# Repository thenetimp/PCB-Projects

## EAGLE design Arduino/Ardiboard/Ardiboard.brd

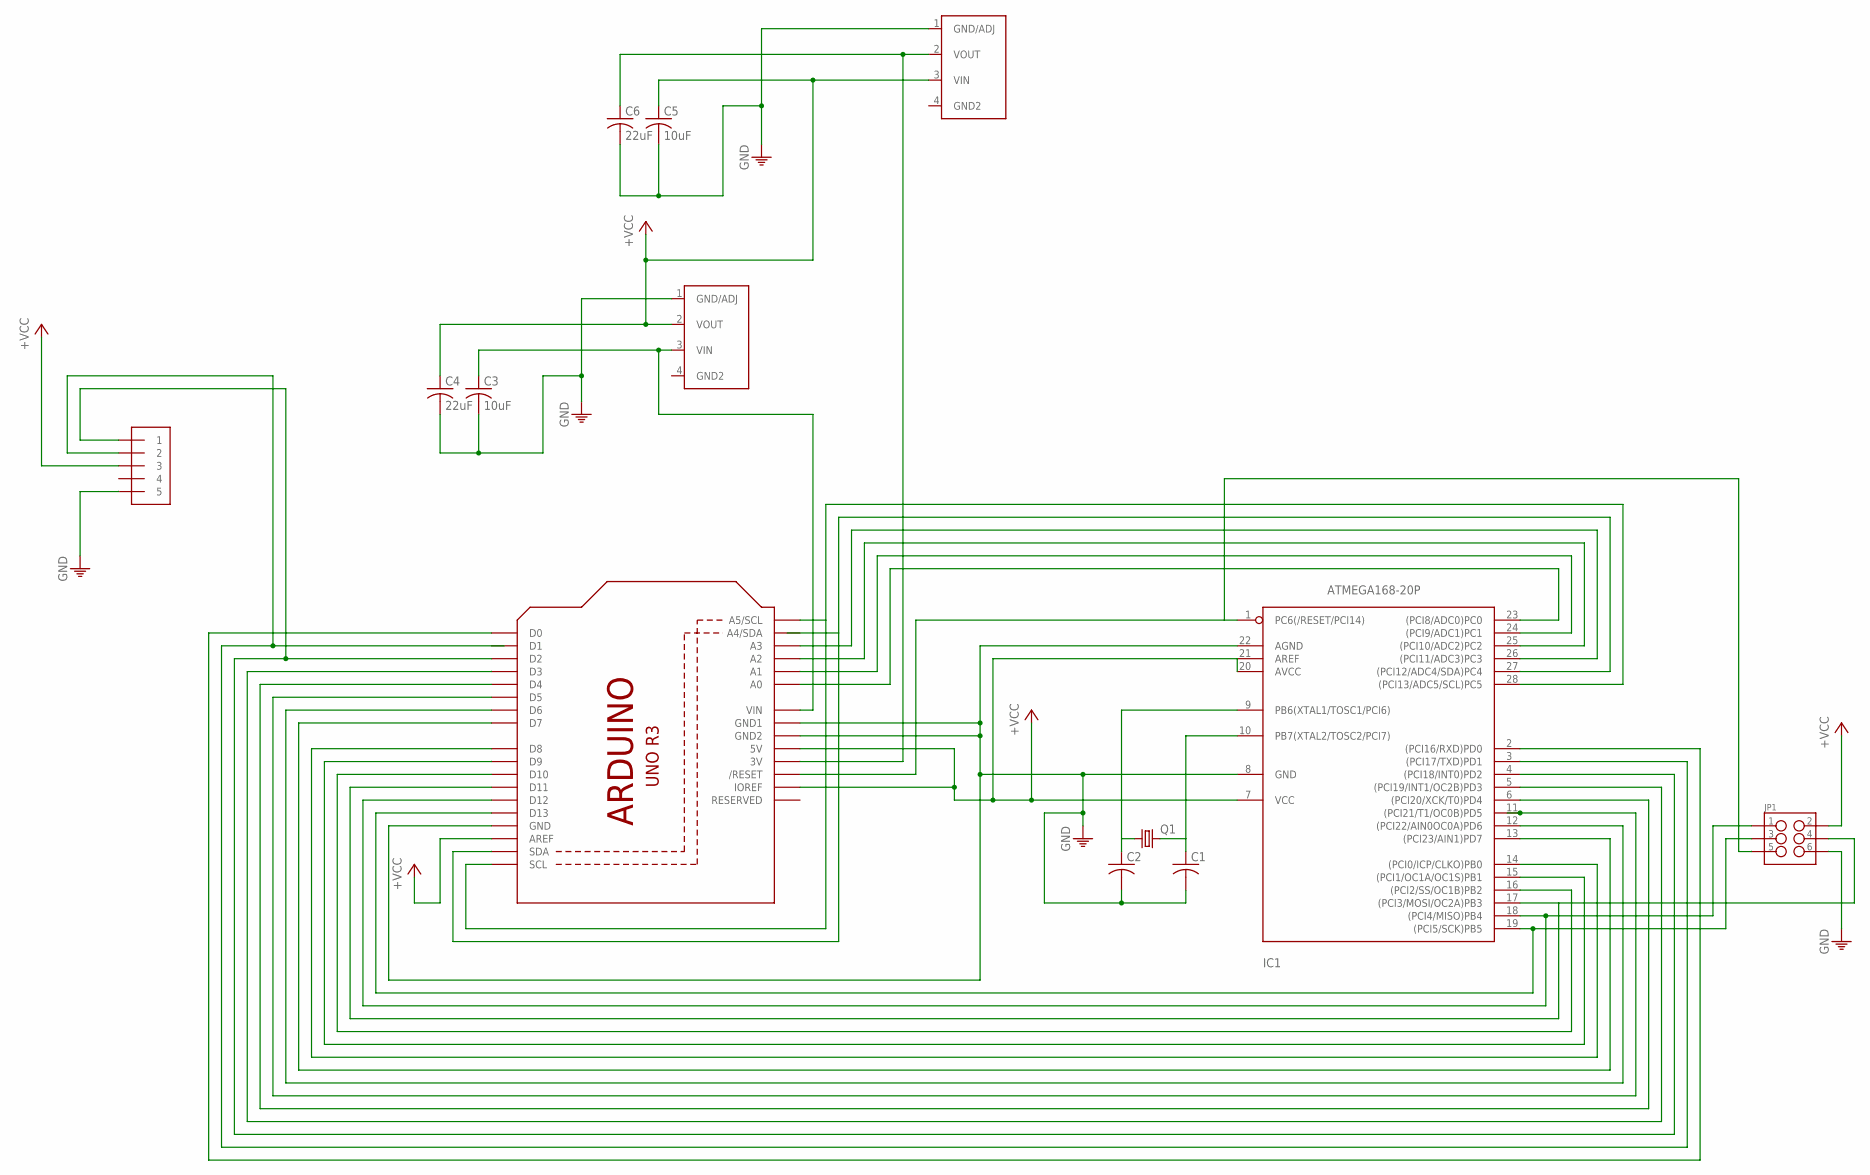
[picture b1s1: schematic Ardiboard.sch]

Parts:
C1, C2: C-US025-025X050; C025-025X050
C3, C5: 10uF; C025-030X050
C4, C6: 22uF; C025-030X050
IC1: ATMEGA168-20P; DIL28-3
J1: 1X5; 1X05-3.5MM
JP1: M03X2; 2X3-SHROUDED
Q1: CRYSTALHC49S; HC49/S
Q2: AZ1086H-5.0; SOT223
Q3: AZ1086H-3.3; SOT223
U1: ARDUINOR3-BPLACE

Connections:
+5V: C4.1, C5.1, IC1.7 (VCC), IC1.20 (AVCC), IC1.21 (AREF), J1.3, JP1.2, Q2.2 (VOUT), Q3.3 (VIN), U1.5V, U1.AREF, U1.IOREF
unnamed: IC1.23 ((PCI8/ADC0)PC0), U1.A0
unnamed: IC1.24 ((PCI9/ADC1)PC1), U1.A1
unnamed: IC1.25 ((PCI10/ADC2)PC2), U1.A2
unnamed: IC1.26 ((PCI11/ADC3)PC3), U1.A3
unnamed: IC1.27 ((PCI12/ADC4/SDA)PC4), U1.SDA
unnamed: IC1.28 ((PCI13/ADC5/SCL)PC5), U1.A5 (A5/SCL), U1.SCL
unnamed: IC1.19 ((PCI5/SCK)PB5), JP1.3, U1.D13
unnamed: IC1.4 ((PCI18/INT0)PD2), J1.1, U1.D2
unnamed: IC1.18 ((PCI4/MISO)PB4), JP1.1, U1.D12
unnamed: IC1.17 ((PCI3/MOSI/OC2A)PB3), JP1.4, U1.D11
unnamed: IC1.16 ((PCI2/SS/OC1B)PB2), U1.D10
unnamed: IC1.15 ((PCI1/OC1A/OC1S)PB1), U1.D9
unnamed: IC1.14 ((PCI0/ICP/CLKO)PB0), U1.D8
unnamed: IC1.13 ((PCI23/AIN1)PD7), U1.D7
unnamed: IC1.12 ((PCI22/AIN0OC0A)PD6), U1.D6
unnamed: IC1.11 ((PCI21/T1/OC0B)PD5), U1.D5
unnamed: IC1.6 ((PCI20/XCK/T0)PD4), U1.D4
unnamed: IC1.5 ((PCI19/INT1/OC2B)PD3), U1.D3
unnamed: IC1.3 ((PCI17/TXD)PD1), J1.2
unnamed: C1.1, IC1.10 (PB7(XTAL2/TOSC2/PCI7)), Q1.2
unnamed: IC1.2 ((PCI16/RXD)PD0), U1.D0
unnamed: IC1.1 (PC6(/RESET/PCI14)), JP1.5, U1.RESET (/RESET)
unnamed: C2.1, IC1.9 (PB6(XTAL1/TOSC1/PCI6)), Q1.1
unnamed: C6.1, Q3.2 (VOUT), U1.3V
unnamed: C3.1, Q2.3 (VIN), U1.VIN
PE: C1.2, C2.2, C3.2, C4.2, C5.2, C6.2, IC1.8 (GND), IC1.22 (AGND), J1.5, JP1.6, Q2.1 (GND/ADJ), Q3.1 (GND/ADJ), U1.GND, U1.GND1, U1.GND2

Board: 2 copper layers, 13 parts (0 on the bottom side), 27 nets, no tracks yet.

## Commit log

2014-05-28 added ardiboard to the repository
2014-05-28 adding empty readme file
2014-05-28 added readme for ardy board
2014-05-28 added data to the readme
2014-06-05 added schematic for ICSP breakout board
2014-06-05 added readme for icsp header breakout board
2014-06-05 renamed file and directory
2014-06-05 edited readme to reflect name change
2014-06-05 adding eagle epf files
2014-06-05 moved Ardiboard project into an arduino directory
2014-06-05 added 3.3V regulator
2014-06-05 changed 3V regulator to pull 5V regulator
2014-06-05 added pull up resistor on reset, and 3.3V regulator pulls from output of 5V, not sure if I'll keep or change that. Removed Ardiboard.brd file since new components were added.

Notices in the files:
parts and their libraries:
SparkFun-Connectors: Licensing: CC v3.0 Share-Alike You are welcome to use this library for commercial purposes.
